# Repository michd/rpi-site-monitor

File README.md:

# Raspberry Pi Site monitor

A dual colour LED-based website monitor for the Raspberry Pi. 

Using red+green 3-pin LEDs, you can create 3 colours: red, green, and yellow. These work well for status indication, so they are a good choice for a website monitor.

There's a bit of python in here that deals with the Raspberry PI's General Purpose In/Out (GPIO) pins, which drives the LEDs. The rest is dealt with through a Bash script.

The bash script first pings a hostname (such as example.com). If it doesn't respond to ping, it will turn the LED to red. If it does respond to ping, it will use curl to determine the HTTP status of a given page on the website. If this status is 200 or 204, it will turn the LED to green. If the HTTP status is anything else, yellow.

If you're better at reading pseudo code instead of text:

```
if (site responds to ping):
  if (page http status is 200 or 204):
    LED color = green
  else:
    LED color = yellow
else:
  LED color = red
```

## Requirements

- Hardware:
  - A Raspberry pi set up with networking
  - Some red+green dual color LEDs (or just a red and green LED per site)
  - NPN transistors to drive the LEDs (BC547-B will do fine)
  - Some resistors (I used 2x 1k Ohm + 2x 220 Ohm per dual colour LED)
  
  Refer to the eagle folder for a schematic and a PCB design with 5 LEDs set up.
- Software:
  - Python
  - Python RPi.GPIO
  - Curl

## Usage

Clone or download the repository, wire up the electronics. In a terminal on your RPi, go to the directory with this code, and run:

```
sudo ./monitor
```

If that doesn't work (probably if you've downloaded this a zip), make `monitor` executable:

```
chmod +x monitor
```

and try running it again. It won't produce any output, and will keep running until you hit Ctrl-C.

### Customise your configuration

By defauly, site monitor uses, you guessed it, default.conf for the configuration. This file contains documented settings and three example websites to status check. To use it for your own sites, make a copy of `default.conf`, and edit it with your favorite text editor. Then, run monitor, specifying your new config as an argument:

```
sudo ./monitor my-config.conf
```

### Console output
To see the status is of the things you're testing, run it with `-v` or `-vv` for more detail:

```
sudo ./monitor -v
```

## To do

See [Issues](https://github.com/michd/rpi-site-monitor/issues) on GitHub.

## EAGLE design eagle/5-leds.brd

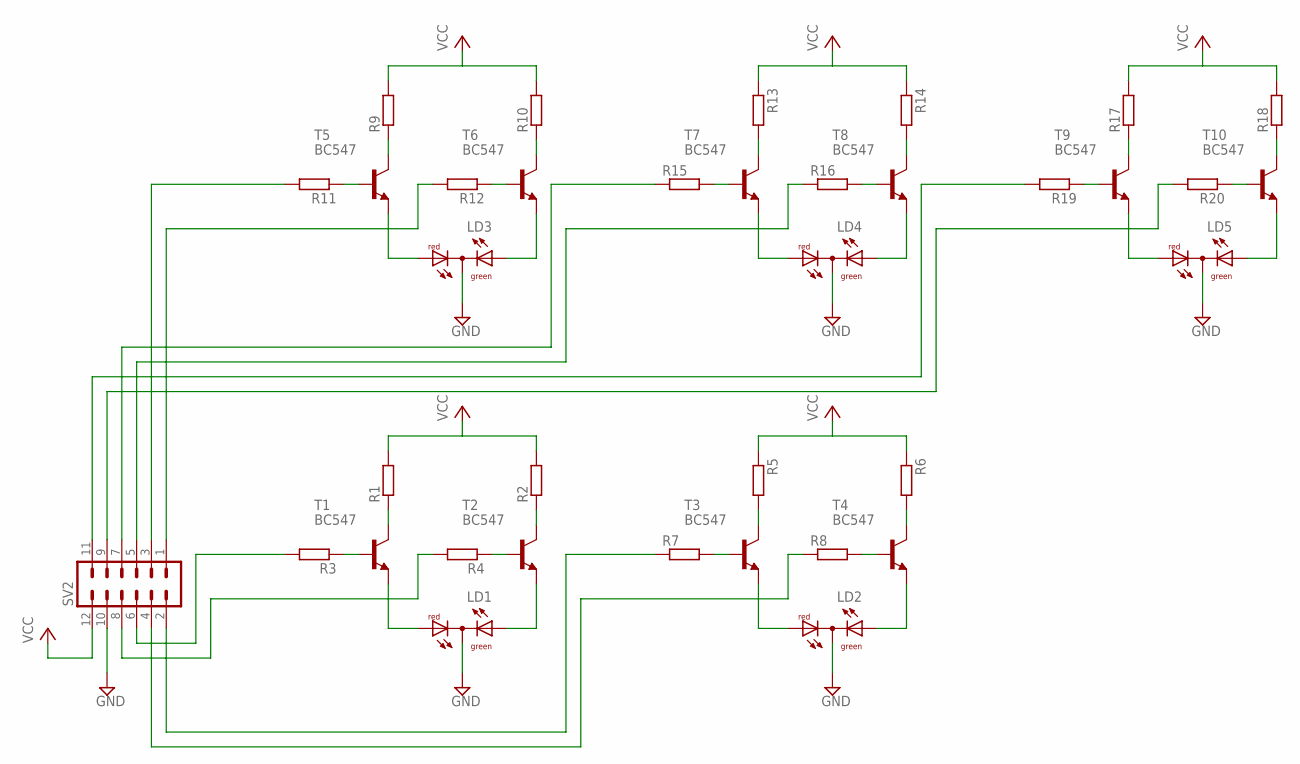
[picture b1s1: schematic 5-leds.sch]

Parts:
LD1, LD2, LD3, LD4, LD5: DUOLED-RG-C; DUOLED-C-5MM
R1, R2, R3, R4, R5, R6, R7, R8, R9, R10, R11, R12, R13, R14, R15, R16, R17, R18, R19, R20: R-EU_0207/7; 0207/7
SV2: MA06-2
T1, T2, T3, T4, T5, T6, T7, T8, T9, T10: BC547; TO92

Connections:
GND: LD1.C, LD2.C, LD3.C, LD4.C, LD5.C, SV2.10
unnamed: LD1.AR, T1.1 (E)
unnamed: LD1.AX (AG), T2.1 (E)
unnamed: R3.1, T1.2 (B)
unnamed: R4.1, T2.2 (B)
unnamed: R4.2, SV2.8
unnamed: R3.2, SV2.6
unnamed: R1.1, T1.3 (C)
unnamed: R2.1, T2.3 (C)
unnamed: LD2.AR, T3.1 (E)
unnamed: LD2.AX (AG), T4.1 (E)
unnamed: R8.1, SV2.4
unnamed: R5.2, T3.3 (C)
unnamed: R6.2, T4.3 (C)
unnamed: R7.2, T3.2 (B)
unnamed: R8.2, T4.2 (B)
unnamed: R7.1, SV2.2
unnamed: LD3.AR, T5.1 (E)
unnamed: LD3.AX (AG), T6.1 (E)
unnamed: R12.2, SV2.1
unnamed: R9.1, T5.3 (C)
unnamed: R10.1, T6.3 (C)
unnamed: R11.1, T5.2 (B)
unnamed: R12.1, T6.2 (B)
unnamed: R11.2, SV2.3
unnamed: LD4.AR, T7.1 (E)
unnamed: LD4.AX (AG), T8.1 (E)
unnamed: R16.1, SV2.5
unnamed: R13.2, T7.3 (C)
unnamed: R14.2, T8.3 (C)
unnamed: R15.2, T7.2 (B)
unnamed: R16.2, T8.2 (B)
unnamed: R15.1, SV2.7
unnamed: LD5.AR, T9.1 (E)
unnamed: LD5.AX (AG), T10.1 (E)
unnamed: R20.2, SV2.9
unnamed: R17.1, T9.3 (C)
unnamed: R18.1, T10.3 (C)
unnamed: R19.1, T9.2 (B)
unnamed: R20.1, T10.2 (B)
unnamed: R19.2, SV2.11
VCC: R1.2, R2.2, R5.1, R6.1, R9.2, R10.2, R13.1, R14.1, R17.2, R18.2, SV2.12

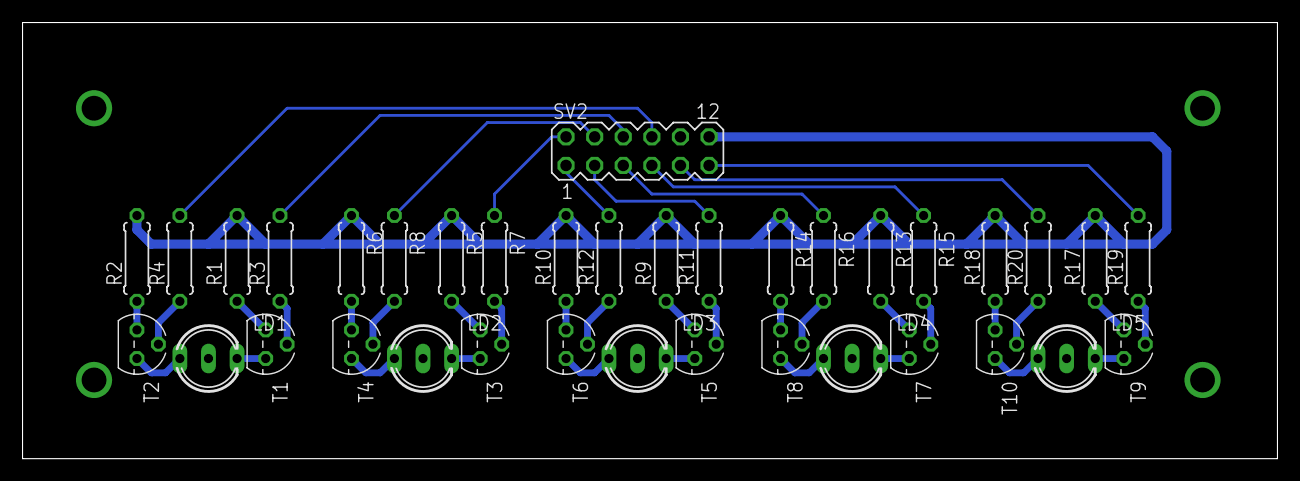
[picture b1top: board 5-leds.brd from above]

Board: 2 copper layers, 111.4 x 38.7 mm, 36 parts (0 on the bottom side), 42 nets.

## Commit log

2015-02-27 Add eagle circuit for board with 5 LEDs
2015-02-28 Tweak schematic, design board
2015-02-28 Update TODO in readme
2015-02-28 Use config files for site / LED pin setup. Closes #1
2015-02-28 Update Readme with stuff about config files
2015-02-28 Readme: some clarification in hardware reqs
2015-03-23 Started working on a box for it in openscad, only have bottom half so far
2015-03-24 Finished generic box, just needs holes for LEDs and connector
2015-03-24 Finish box design
